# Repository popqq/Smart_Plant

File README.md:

[![Documentation Status][documentation-shield]][documentation]
[![License][license-shield]](LICENSE)
[![Project Maintenance][maintenance-shield]][maintenance]
[![buyit][buyit-shield]][buyit]

# Smart Plant
The Smart Plant is a board that can be plugged directly on the soil, close to the plant, that allows the measurement of the environment (soil moisture, environment temperature & illuminance), and presents the information on an ePaper display.

## Project tree

<li><a href="./Design/">Design</a></li>
<li><a href="./Documentation/">Documentation</a></li>

<li><a href="./README.md">README.md</a></li>

[documentation-shield]: https://readthedocs.org/projects/smart-plant/badge/?version=v2r1&style=for-the-badge
[documentation]: https://smart-plant.readthedocs.io/

[license-shield]: https://img.shields.io/badge/License-CC%20BY--NC--SA%204.0-lightgrey.svg?style=for-the-badge

[maintenance-shield]: https://img.shields.io/badge/maintainer-J.%20G.%20Aguado-2e48a7.svg?style=for-the-badge
[maintenance]: https://github.com/JGAguado

[buyit-shield]: https://img.shields.io/badge/get%20it%20on-elecrow-399BD7.svg?style=for-the-badge
[buyit]: https://www.elecrow.com/smart-plant.html

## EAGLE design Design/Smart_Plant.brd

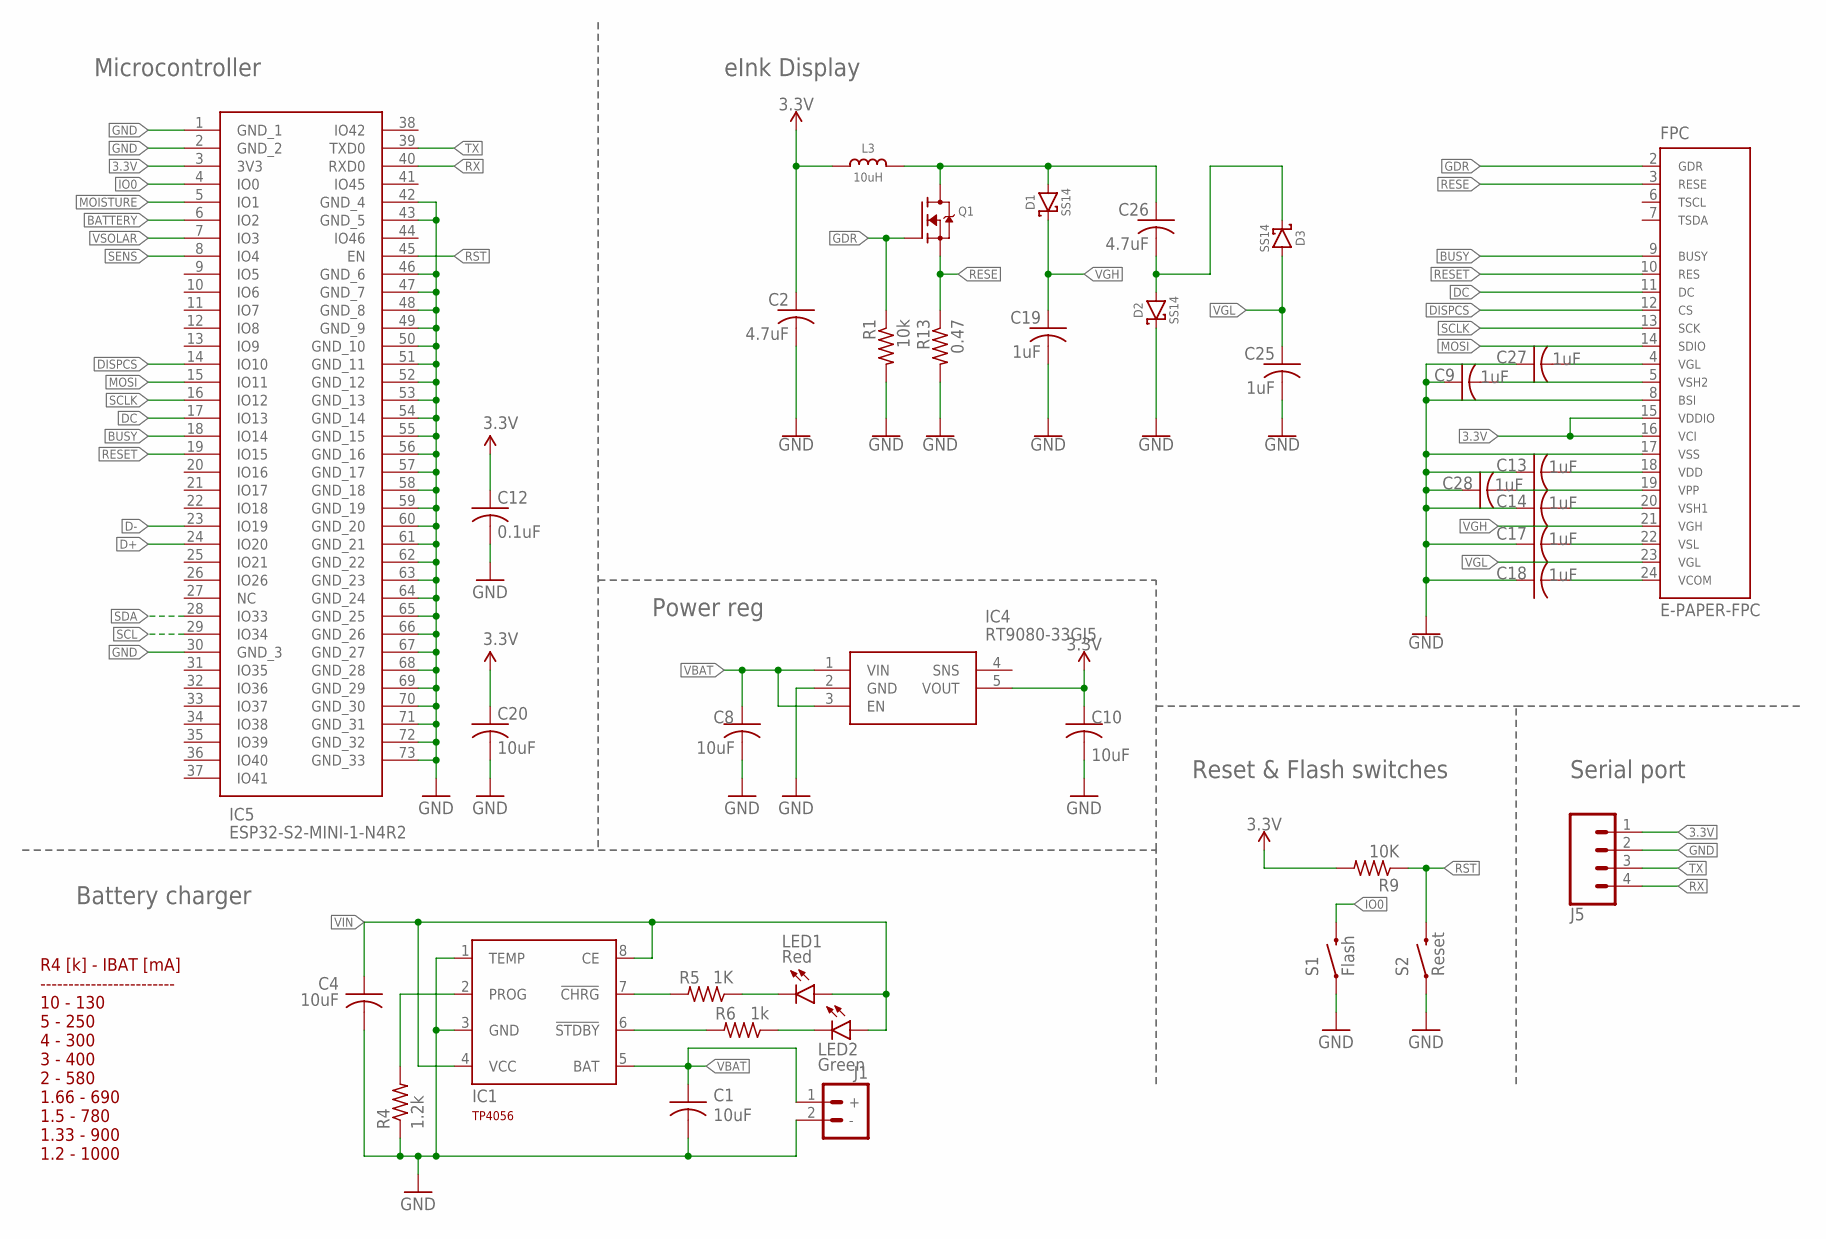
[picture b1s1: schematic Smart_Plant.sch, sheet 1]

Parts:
C1, C4, C8, C10, C20: 10uF; C0603
C2, C26: 4.7uF; C0603
C9, C13, C14, C17, C18, C19, C25, C27, C28: 1uF; C0603
C12: 0.1uF; C0603
D1, D2, D3: SS14; SMA-DIODE
FPC: E-PAPER-FPC; FPC_24_0.5MM
IC1: TP4056; SOT23-8; LCSC C16581
IC4: RT9080-33GJ5; SOT94P280X100-5N; LCSC C841192
IC5: ESP32-S2-MINI-1-N4R2; ESP32S2MINI1N4R2
J1: BAT_CONN-JST-2MM-SMT; JST-2-SMD
J5: CONN_04PTH; 1X04
L3: 10uH; INDUCTOR_4X4MM_NR401
LED1: Red; LED_0603; LCSC C2286
LED2: Green; LED_0603; LCSC C72043
Q1: IRLML0100; SOT23-3
R1: 10k; R0603
R4: 1.2k; R0603
R5: 1K; R0603
R6: 1k; R0603
R9: 10K; R0603
R13: 0.47; R0603
S1: Flash; TACTILE_SWITCH_SMD_5.2MM
S2: Reset; TACTILE_SWITCH_SMD_5.2MM

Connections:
3.3V: C2.1, C10.1, C12.1, C20.1, FPC.15, FPC.16, IC4.5 (VOUT), IC5.3 (3V3), J5.1, L3.P$2 (2), R9.2; also elsewhere on the board
BATTERY: IC5.6 (IO2); also elsewhere on the board
BUSY: FPC.9, IC5.18 (IO14)
D+: IC5.24 (IO20); also elsewhere on the board
D-: IC5.23 (IO19); also elsewhere on the board
DC: FPC.11, IC5.17 (IO13)
DISPCS: FPC.12, IC5.14 (IO10)
GDR: FPC.2, Q1.1 (G), R1.1
GND: C1.2, C2.2, C4.2, C8.2, C9.1, C10.2, C12.2, C13.1, C14.1, C17.1, C18.1, C19.2, C20.2, C25.2, C27.1, C28.1, D2.C, FPC.8, FPC.17, IC1.1 (TEMP), IC1.3 (GND), IC4.2 (GND), IC5.1 (GND_1), IC5.2 (GND_2), IC5.30 (GND_3), IC5.42 (GND_4), IC5.43 (GND_5), IC5.46 (GND_6), IC5.47 (GND_7), IC5.48 (GND_8), IC5.49 (GND_9), IC5.50 (GND_10), IC5.51 (GND_11), IC5.52 (GND_12), IC5.53 (GND_13), IC5.54 (GND_14), IC5.55 (GND_15), IC5.56 (GND_16), IC5.57 (GND_17), IC5.58 (GND_18), IC5.59 (GND_19), IC5.60 (GND_20), IC5.61 (GND_21), IC5.62 (GND_22), IC5.63 (GND_23), IC5.64 (GND_24), IC5.65 (GND_25), IC5.66 (GND_26), IC5.67 (GND_27), IC5.68 (GND_28), IC5.69 (GND_29), IC5.70 (GND_30), IC5.71 (GND_31), IC5.72 (GND_32), IC5.73 (GND_33), J1.2 (-), J5.2, R1.2, R4.1, R13.2, S1.1, S2.1; also elsewhere on the board
IO0: IC5.4 (IO0), S1.3 (2)
MOISTURE: IC5.5 (IO1); also elsewhere on the board
MOSI: FPC.14, IC5.15 (IO11)
unnamed: IC1.6 (!STDBY), R6.2
unnamed: LED1.C, R5.1
unnamed: LED2.C, R6.1
unnamed: IC1.2 (PROG), R4.2
unnamed: IC1.7 (!CHRG), R5.2
unnamed: C9.2, FPC.5
unnamed: C13.2, FPC.18
unnamed: C14.2, FPC.20
unnamed: C17.2, FPC.22
unnamed: C18.2, FPC.24
unnamed: C26.2, D2.A, D3.C
unnamed: C26.1, D1.A, L3.P$1 (1), Q1.3 (D)
unnamed: C27.2, FPC.4
unnamed: C28.2, FPC.19
RESE: FPC.3, Q1.2 (S), R13.1
RESET: FPC.10, IC5.19 (IO15)
RST: IC5.45 (EN), R9.1, S2.3 (2)
RX: IC5.40 (RXD0), J5.4
SCL: IC5.29 (IO34); also elsewhere on the board
SCLK: FPC.13, IC5.16 (IO12)
SDA: IC5.28 (IO33); also elsewhere on the board
SENS: IC5.8 (IO4); also elsewhere on the board
TX: IC5.39 (TXD0), J5.3
VBAT: C1.1, C8.1, IC1.5 (BAT), IC4.1 (VIN), IC4.3 (EN), J1.1 (+); also elsewhere on the board
VGH: C19.1, D1.C, FPC.21
VGL: C25.1, D3.A, FPC.23
VIN: C4.1, IC1.4 (VCC), IC1.8 (CE), LED1.A, LED2.A; also elsewhere on the board
VSOLAR: IC5.7 (IO3); also elsewhere on the board

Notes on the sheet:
Microcontroller
eInk Display
Serial port
R4 [k] - IBAT [mA] ------------------------ 10 - 130 5 - 250 4 - 300 3 - 400 2 - 580 1.66 - 690 1.5 - 780 1.33 - 900 1.2 - 1000
Battery charger
Power reg
Reset & Flash switches

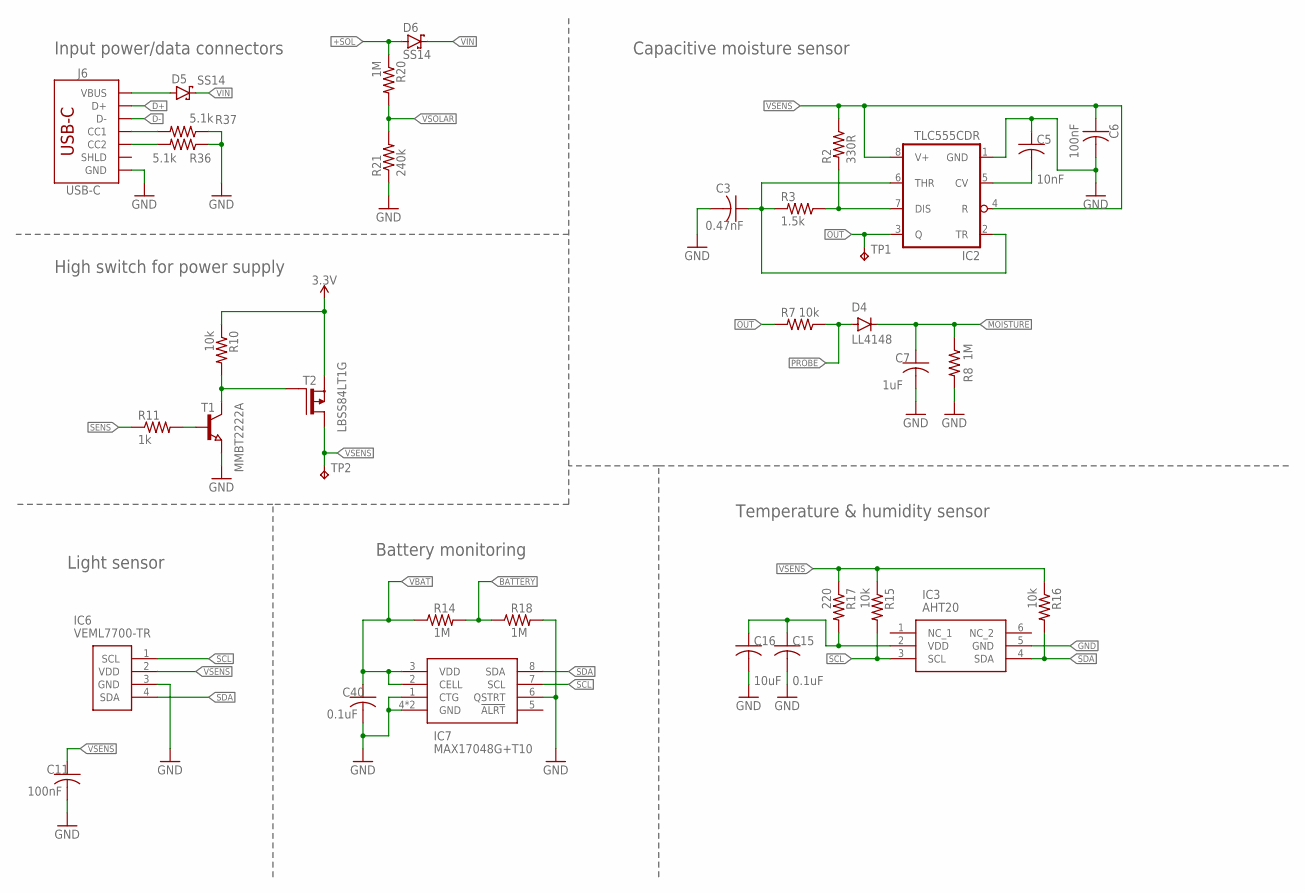
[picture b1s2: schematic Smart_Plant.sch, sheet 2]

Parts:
C3: 0.47nF; C0603
C5: 10nF; C0603
C6, C11: 100nF; C0603
C7: 1uF; C0603
C15, C40: 0.1uF; C0603
C16: 10uF; C0603
D4: LL4148; LL-34
D5, D6: SS14; SMA-DIODE
IC2: TLC555CDR; SO08
IC3: AHT20
IC6: VEML7700-TR
IC7: MAX17048G+T10; SON50P200X200X80-9N
J6: USB-C; USB-C-16P-4LAYER-ISOLATED; LCSC C2765186
R2: 330R; R0603
R3: 1.5k; R0603
R7, R10, R15, R16: 10k; R0603
R8, R14, R18, R20: 1M; R0603
R11: 1k; R0603
R17: 220; R0603
R21: 240k; R0603
R36, R37: 5.1k; R0603
T1: MMBT2222A; SOT23
T2: LBSS84LT1G; SOT23
TP1, TP2: TPB1,27; B1,27

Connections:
3.3V: R10.1, T2.2 (S); also elsewhere on the board
+SOL: D6.A, R20.1
BATTERY: R14.2, R18.1; also elsewhere on the board
D+: J6.A6 (D+), J6.B6 (D+); also elsewhere on the board
D-: J6.A7 (D-), J6.B7 (D-); also elsewhere on the board
GND: C3.2, C5.1, C6.2, C7.2, C11.2, C15.2, C16.2, C40.2, IC2.1 (GND), IC3.5 (GND), IC6.3 (GND), IC7.1 (CTG), IC7.4 (GND), IC7.6 (QSTRT), IC7.9 (GND), J6.GND, J6.GND2 (GND), R8.2, R18.2, R21.1, R36.1, R37.1, T1.2 (E); also elsewhere on the board
MOISTURE: C7.1, D4.C, R8.1; also elsewhere on the board
unnamed: C3.1, IC2.2 (TR), IC2.6 (THR), R3.2
unnamed: IC2.7 (DIS), R2.2, R3.1
unnamed: C5.2, IC2.5 (CV)
unnamed: R10.2, T1.3 (C), T2.1 (G)
unnamed: C15.1, C16.1, IC3.2 (VDD), R17.2
unnamed: R11.2, T1.1 (B)
unnamed: J6.B5 (CC2), R36.2
unnamed: J6.A5 (CC1), R37.2
OUT: IC2.3 (Q), R7.2, TP1.TP
PROBE: D4.A, R7.1
SCL: IC3.3 (SCL), IC6.1 (SCL), IC7.7 (SCL), R15.2; also elsewhere on the board
SDA: IC3.4 (SDA), IC6.4 (SDA), IC7.8 (SDA), R16.2; also elsewhere on the board
SENS: R11.1; also elsewhere on the board
VBAT: C40.1, IC7.2 (CELL), IC7.3 (VDD), R14.1; also elsewhere on the board
VIN: D5.C, D6.C; also elsewhere on the board
VSENS: C6.1, C11.1, IC2.4 (R), IC2.8 (V+), IC6.2 (VDD), R2.1, R15.1, R16.1, R17.1, T2.3 (D), TP2.TP
VSOLAR: R20.2, R21.2; also elsewhere on the board
V_USB: D5.A, J6.VBUS1 (VBUS), J6.VBUS2 (VBUS)

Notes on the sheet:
Capacitive moisture sensor
High switch for power supply
Light sensor
Temperature & humidity sensor
Battery monitoring
Input power/data connectors

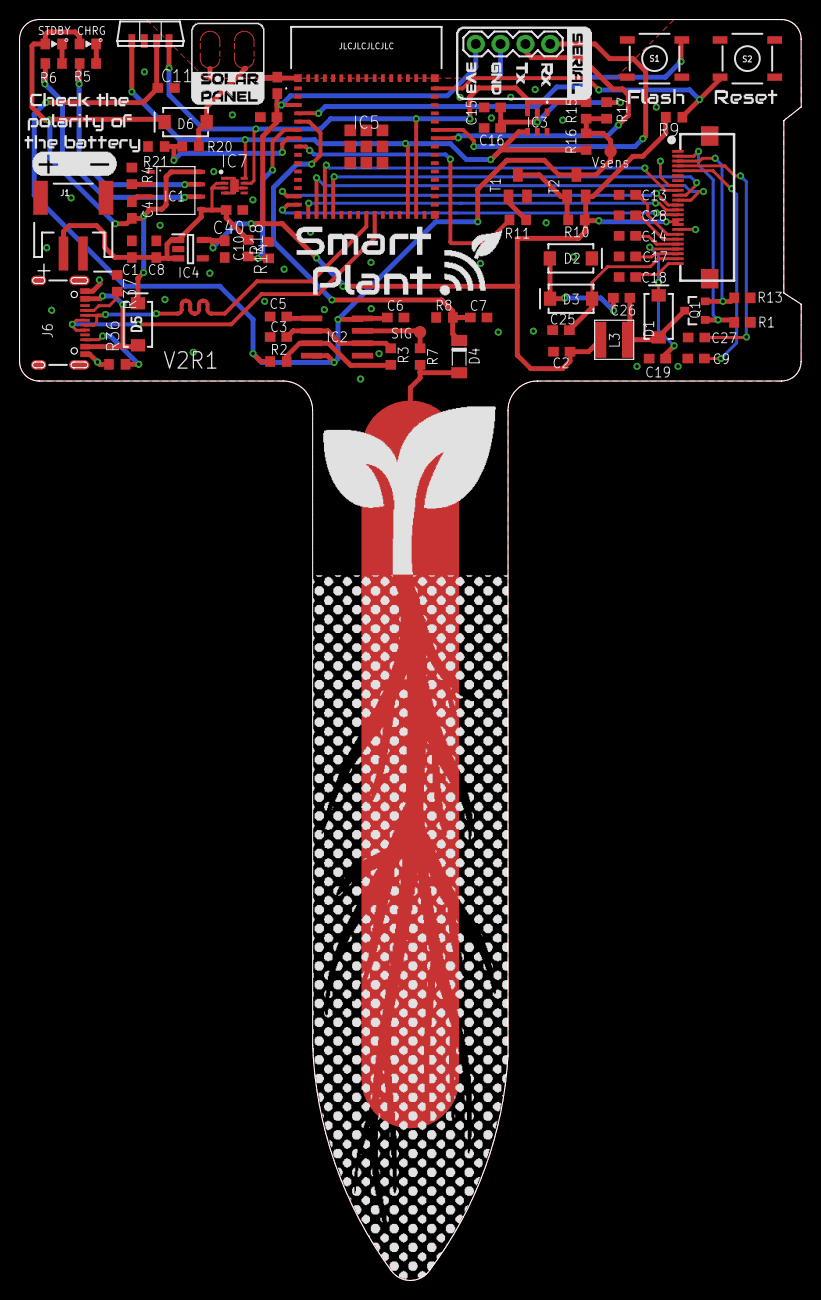
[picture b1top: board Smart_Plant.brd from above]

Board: 2 copper layers, 80.0 x 129.1 mm, 73 parts (0 on the bottom side), 53 nets.

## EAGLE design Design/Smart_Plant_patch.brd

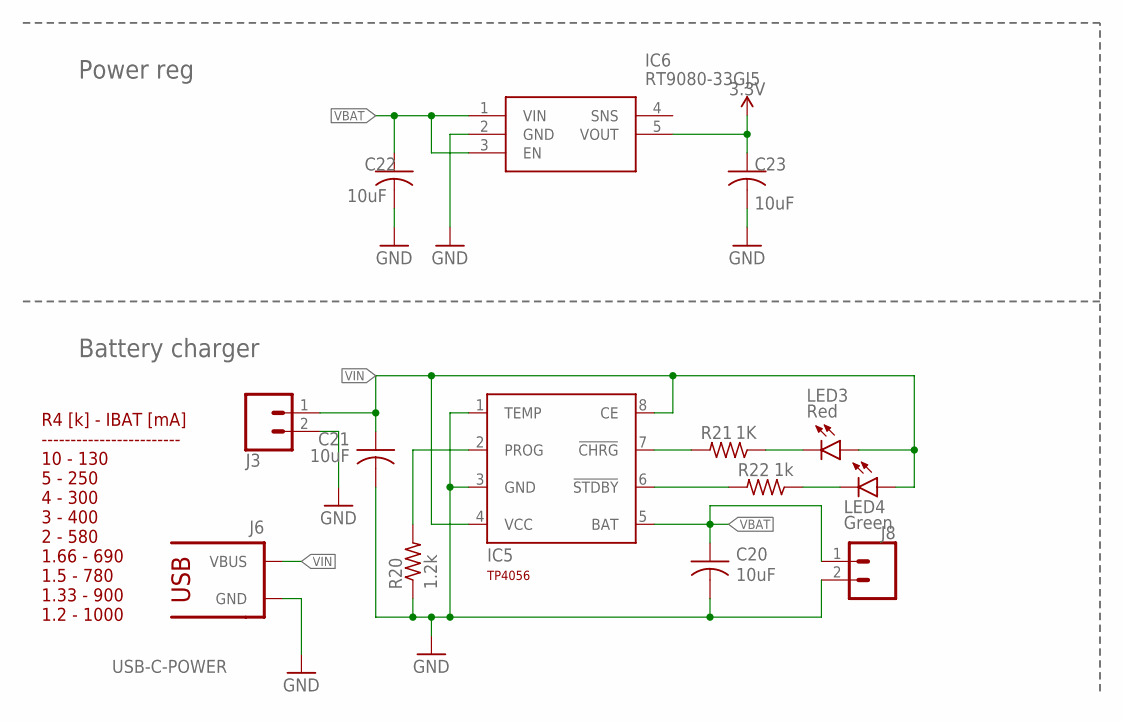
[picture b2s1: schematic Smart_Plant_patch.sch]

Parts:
C20, C21, C22, C23: 10uF; C0603
IC5: TP4056; SOT23-8
IC6: RT9080-33GJ5; SOT94P280X100-5N; LCSC C841192
J3: CONN_02; 1X02
J6: USB-C-POWER
J8: CONN_02-JST-2MM-SMT; JST-2-SMD; LCSC C3029440
LED3: Red; LED_0603
LED4: Green; LED_0603
R20: 1.2k; R0603
R21: 1K; R0603
R22: 1k; R0603

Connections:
3.3V: C23.1, IC6.5 (VOUT)
GND: C20.2, C21.2, C22.2, C23.2, IC5.1 (TEMP), IC5.3 (GND), IC6.2 (GND), J3.2, J6.GND, J8.2 (1), R20.1
unnamed: IC5.6 (!STDBY), R22.2
unnamed: LED3.C, R21.1
unnamed: LED4.C, R22.1
unnamed: IC5.2 (PROG), R20.2
unnamed: IC5.7 (!CHRG), R21.2
VBAT: C20.1, C22.1, IC5.5 (BAT), IC6.1 (VIN), IC6.3 (EN), J8.1 (2)
VIN: C21.1, IC5.4 (VCC), IC5.8 (CE), J3.1, J6.VBUS, LED3.A, LED4.A

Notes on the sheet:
R4 [k] - IBAT [mA] ------------------------ 10 - 130 5 - 250 4 - 300 3 - 400 2 - 580 1.66 - 690 1.5 - 780 1.33 - 900 1.2 - 1000
Battery charger
Power reg

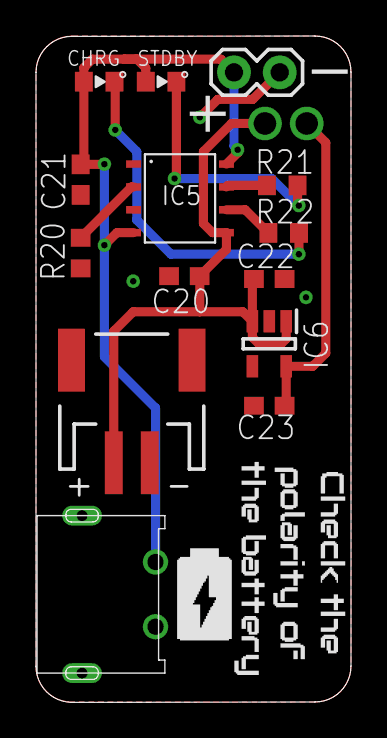
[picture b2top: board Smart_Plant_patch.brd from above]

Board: 2 copper layers, 17.5 x 37.0 mm, 14 parts (0 on the bottom side), 9 nets.

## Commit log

2022-10-02 Updated design files for Smart_Plant
2022-10-02 Added datasheets
2022-10-02 Added silkscreen files
2022-10-06 Update design files
2022-10-06 updated Silkscreen
2022-10-22 Resistors charger note
2022-10-23 Added Documentation/Images
2022-11-01 docs
2022-11-08 Added pictures
2023-02-12 Added power patch
2023-02-12 Updated images
2023-02-12 Added schematics to documentation
2023-02-12 Added enclosure 3d files
2023-03-11 Released designs from V1R1 with the patch board
2023-03-15 Updated configuration.yaml
2023-04-02 Added designs for V1R2
2023-04-02 Updated Documentation for V1R2
2023-04-02 Added enclosure files for V1R2
2023-04-02 Updated docs for R1V2
2023-04-02 Updated schematics
2023-06-27 SoC first draft
2023-07-02 Updated enclosure files
2023-08-11 Design V1R3
2023-08-11 Silkscreen V1R3
2023-08-16 First draft of the V2R1 design
2023-11-12 Updated Documentation for V2R1
2023-11-12 Added enclosures
2023-11-12 gitignore modified
2023-11-12 Enclosures update
2023-12-29 Restructured Enclosure folder with updated files
2024-01-30 Added STP files
2024-01-31 Update configuration.yaml
    issue was lux -> lx in order to have it work in homeassistant
2024-05-03 Readme
2024-12-07 Add pinout

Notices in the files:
parts and their libraries:
microbuilder: This work is placed in the public domain, and may be freely used for commercial and non-commercial work with the following conditions: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
SparkFun-Connectors: Licensing: Creative Commons ShareAlike 4.0 International - https://creativecommons.org/licenses/by-sa/4.0
